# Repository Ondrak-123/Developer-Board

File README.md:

# RP2040 Developer Board
This project was great for learning something about the RP2040 ecosystem, great thing about this dev board is 16MB FLASH and 30 GPIOS.
You can use this developer board in breadboards, custom builds and any other way you can think of!

_**Featuring:**_
 
**MCU: Dual-core Arm Cortex-M0+ @ 133MHz.**

**Storage: 16MB (128Mbit) SPI Flash**

**Power: 3.3V LDO (MCP1700), up to 250mA.**

**Interface: USB-C 2.0 for programming and power.**

**Button for easy flashing.**

**This build features 0402 and QFLN parts so you will need some experience, steady hands, stencil and a solder paste/flux.**

**HOW TO FLASH:**
- This board supports the standard RP2040 bootloader
- Connect the board to your PC via USB-C
- Hold down the BOOTSEL button.
- The board will appear as a mass storage device
- Drag and drop your .uf2 file

**BOM:**

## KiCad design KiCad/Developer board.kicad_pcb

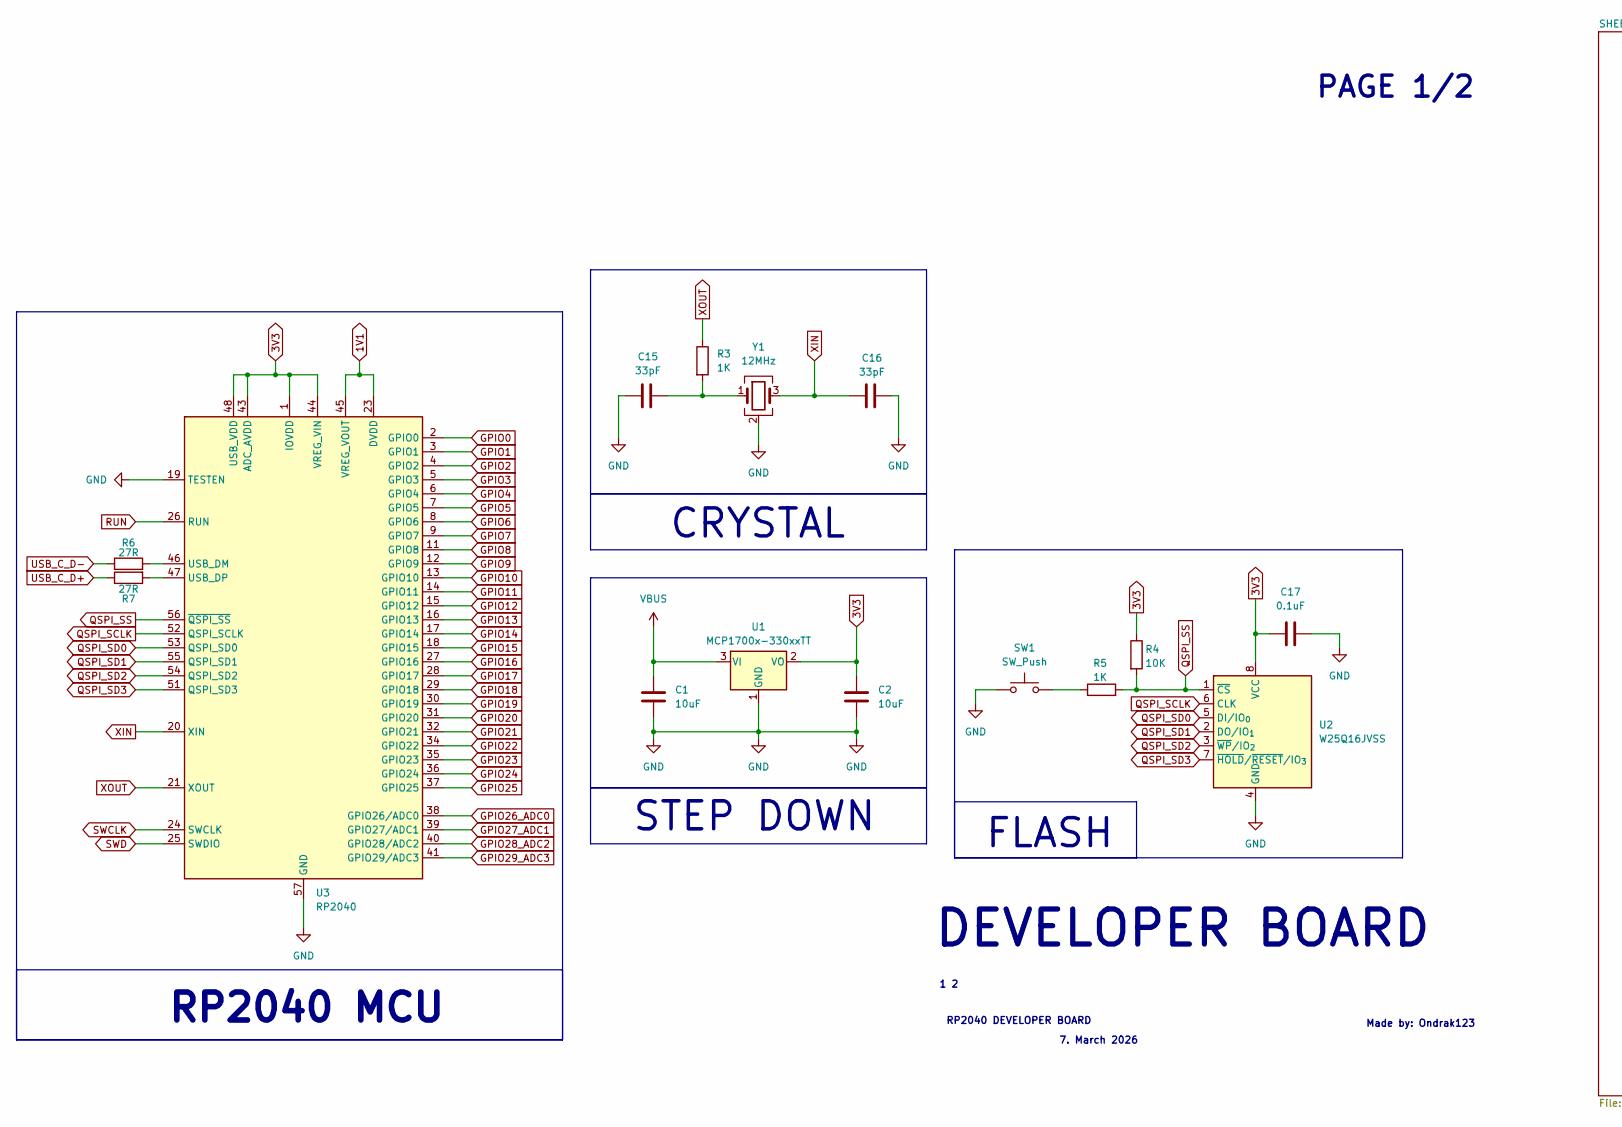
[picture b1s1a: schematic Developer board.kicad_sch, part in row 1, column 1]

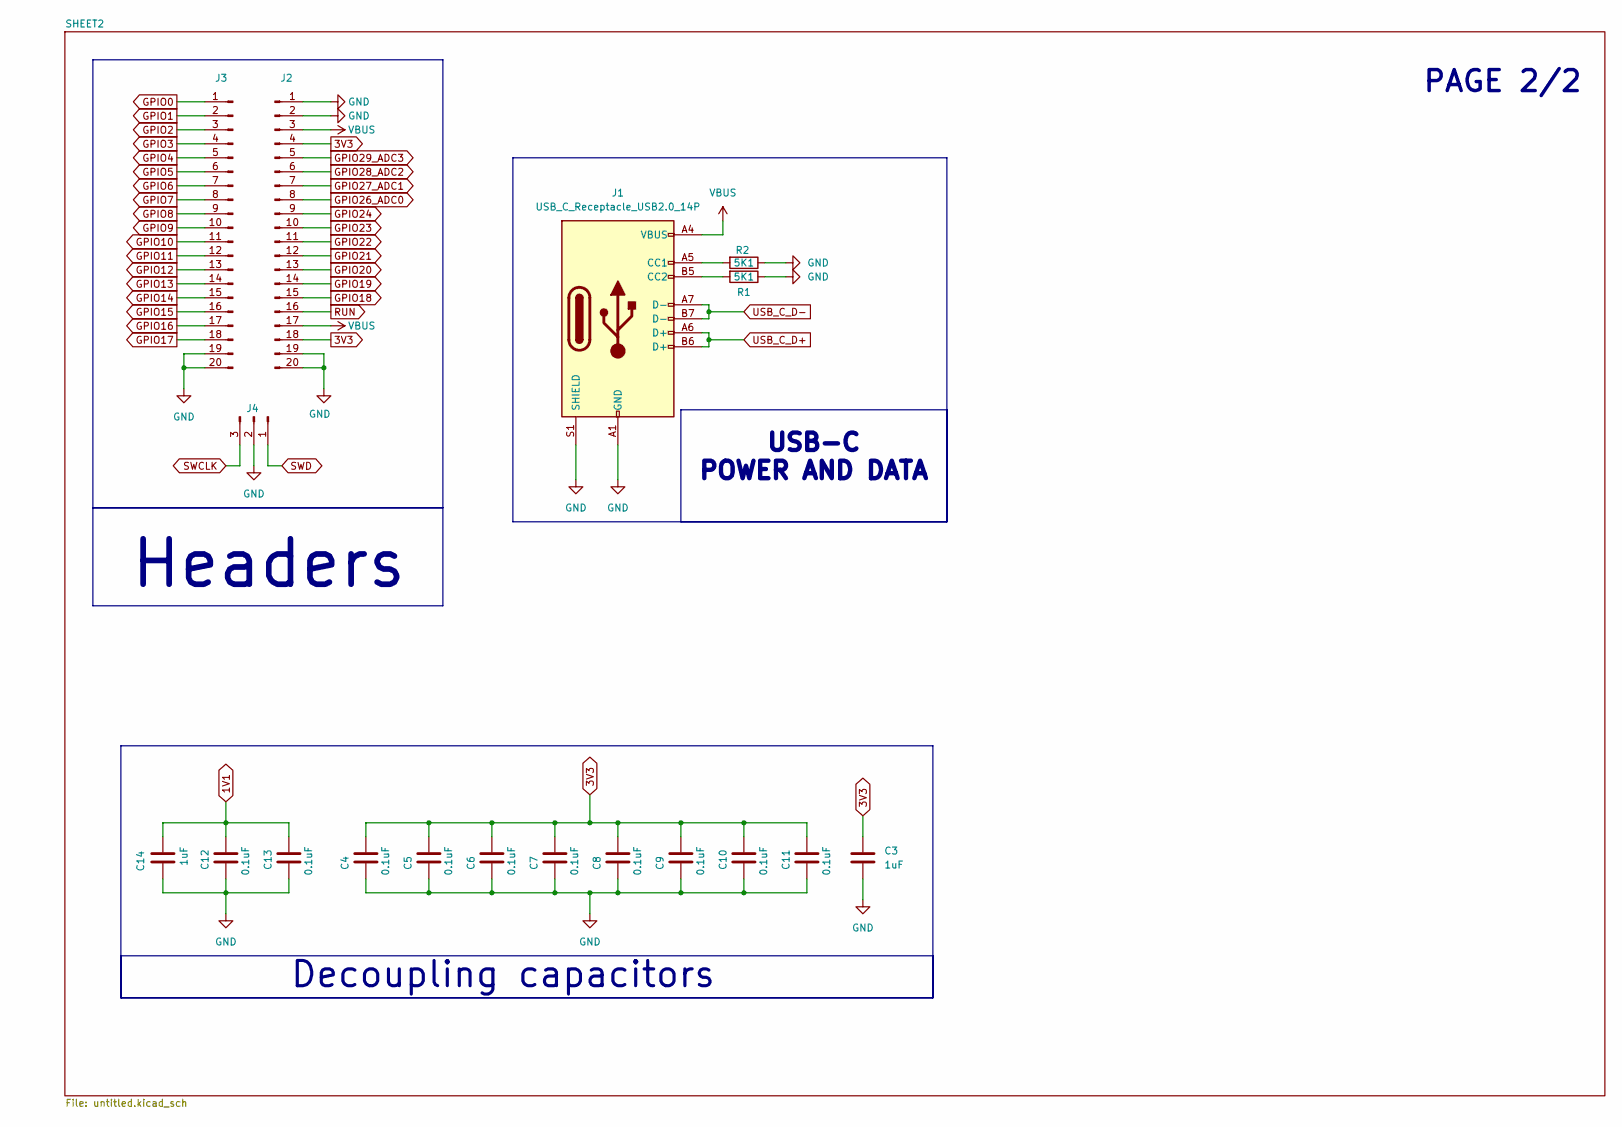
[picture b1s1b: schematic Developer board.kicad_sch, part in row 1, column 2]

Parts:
C1, C2: 10uF; C_0603_1608Metric
C3, C14: 1uF; C_0603_1608Metric
C4, C5, C6, C7, C8, C9, C10, C11, C12, C13, C17: 0.1uF; C_0402_1005Metric_Pad0.74x0.62mm_HandSolder
C15, C16: 33pF; C_0402_1005Metric_Pad0.74x0.62mm_HandSolder
J1: USB_C_Receptacle_USB2.0_14P; USB_C_Receptacle_GCT_USB4105-xx-A_16P_TopMnt_Horizontal
J2, J3: Conn_01x20_Pin; PinHeader_1x20_P2.54mm_Vertical
J4: Conn_01x03_Pin; PinHeader_1x03_P2.54mm_Vertical
R1, R2: 5K1; R_0402_1005Metric_Pad0.72x0.64mm_HandSolder
R3, R5: 1K; R_0402_1005Metric_Pad0.72x0.64mm_HandSolder
R4: 10K; R_0402_1005Metric_Pad0.72x0.64mm_HandSolder
R6, R7: 27R; R_0402_1005Metric_Pad0.72x0.64mm_HandSolder
SW1: SW_Push; SW_Push_SPST_NO_Alps_SKRK
U1: MCP1700x-330xxTT; SOT-23
U2: W25Q16JVSS; SOIC-8_5.3x5.3mm_P1.27mm
U3: RP2040; QFN-56-1EP_7x7mm_P0.4mm_EP3.2x3.2mm
Y1: 12MHz; Crystal_SMD_3225-4Pin_3.2x2.5mm_HandSoldering

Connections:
1V1: C12.1, C13.1, C14.1, U3.23 (DVDD), U3.45 (VREG_VOUT), U3.50 (DVDD)
3V3: C2.1, C3.1, C4.1, C5.1, C6.1, C7.1, C8.1, C9.1, C10.1, C11.1, C17.1, J2.4, J2.18, R4.1, U1.2 (VO), U2.8 (VCC), U3.1 (IOVDD), U3.10 (IOVDD), U3.22 (IOVDD), U3.33 (IOVDD), U3.42 (IOVDD), U3.43 (ADC_AVDD), U3.44 (VREG_VIN), U3.48 (USB_VDD), U3.49 (IOVDD)
GND: C1.2, C2.2, C3.2, C4.2, C5.2, C6.2, C7.2, C8.2, C9.2, C10.2, C11.2, C12.2, C13.2, C14.2, C15.1, C16.1, C17.2, J1.A1 (GND), J1.A12 (GND), J1.B1 (GND), J1.B12 (GND), J1.S1 (SHIELD), J2.1, J2.2, J2.19, J2.20, J3.19, J3.20, J4.2, R1.1, R2.1, SW1.1, U1.1 (GND), U2.4 (GND), U3.19 (TESTEN), U3.57 (GND), Y1.2 (G), Y1.4 (G)
GPIO0: J3.1, U3.2 (GPIO0)
GPIO1: J3.2, U3.3 (GPIO1)
GPIO2: J3.3, U3.4 (GPIO2)
GPIO3: J3.4, U3.5 (GPIO3)
GPIO4: J3.5, U3.6 (GPIO4)
GPIO5: J3.6, U3.7 (GPIO5)
GPIO6: J3.7, U3.8 (GPIO6)
GPIO7: J3.8, U3.9 (GPIO7)
GPIO8: J3.9, U3.11 (GPIO8)
GPIO9: J3.10, U3.12 (GPIO9)
GPIO10: J3.11, U3.13 (GPIO10)
GPIO11: J3.12, U3.14 (GPIO11)
GPIO12: J3.13, U3.15 (GPIO12)
GPIO13: J3.14, U3.16 (GPIO13)
GPIO14: J3.15, U3.17 (GPIO14)
GPIO15: J3.16, U3.18 (GPIO15)
GPIO16: J3.17, U3.27 (GPIO16)
GPIO17: J3.18, U3.28 (GPIO17)
GPIO18: J2.15, U3.29 (GPIO18)
GPIO19: J2.14, U3.30 (GPIO19)
GPIO20: J2.13, U3.31 (GPIO20)
GPIO21: J2.12, U3.32 (GPIO21)
GPIO22: J2.11, U3.34 (GPIO22)
GPIO23: J2.10, U3.35 (GPIO23)
GPIO24: J2.9, U3.36 (GPIO24)
GPIO25: U3.37 (GPIO25)
GPIO26_ADC0: J2.8, U3.38 (GPIO26/ADC0)
GPIO27_ADC1: J2.7, U3.39 (GPIO27/ADC1)
GPIO28_ADC2: J2.6, U3.40 (GPIO28/ADC2)
GPIO29_ADC3: J2.5, U3.41 (GPIO29/ADC3)
unnamed: C15.2, R3.2, Y1.1
unnamed: J1.A5 (CC1), R2.2
unnamed: J1.B5 (CC2), R1.2
unnamed: R5.1, SW1.2
unnamed: R6.2, U3.46 (USB_DM)
unnamed: R7.2, U3.47 (USB_DP)
QSPI_SCLK: U2.6 (CLK), U3.52 (QSPI_SCLK)
QSPI_SD0: U2.5 (DI/IO_{0}), U3.53 (QSPI_SD0)
QSPI_SD1: U2.2 (DO/IO_{1}), U3.55 (QSPI_SD1)
QSPI_SD2: U2.3 (~WP/IO_{2}), U3.54 (QSPI_SD2)
QSPI_SD3: U2.7 (~HOLD/~RESET/IO_{3}), U3.51 (QSPI_SD3)
QSPI_SS: R4.2, R5.2, U2.1 (~CS), U3.56 (~QSPI_SS)
RUN: J2.16, U3.26 (RUN)
SWCLK: J4.3, U3.24 (SWCLK)
SWD: J4.1, U3.25 (SWDIO)
USB_C_D+: J1.A6 (D+), J1.B6 (D+), R7.1
USB_C_D-: J1.A7 (D-), J1.B7 (D-), R6.1
VBUS: C1.1, J1.A4 (VBUS), J1.A9 (VBUS), J1.B4 (VBUS), J1.B9 (VBUS), J2.3, J2.17, U1.3 (VI)
XIN: C16.2, U3.20 (XIN), Y1.3
XOUT: R3.1, U3.21 (XOUT)

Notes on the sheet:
STEP DOWN
Made by: Ondrak123
PAGE 2/2
1 2
RP2040 MCU
PAGE 1/2
CRYSTAL
DEVELOPER BOARD
FLASH
Headers
7. March 2026
Decoupling capacitors
USB-C POWER AND DATA
RP2040 DEVELOPER BOARD

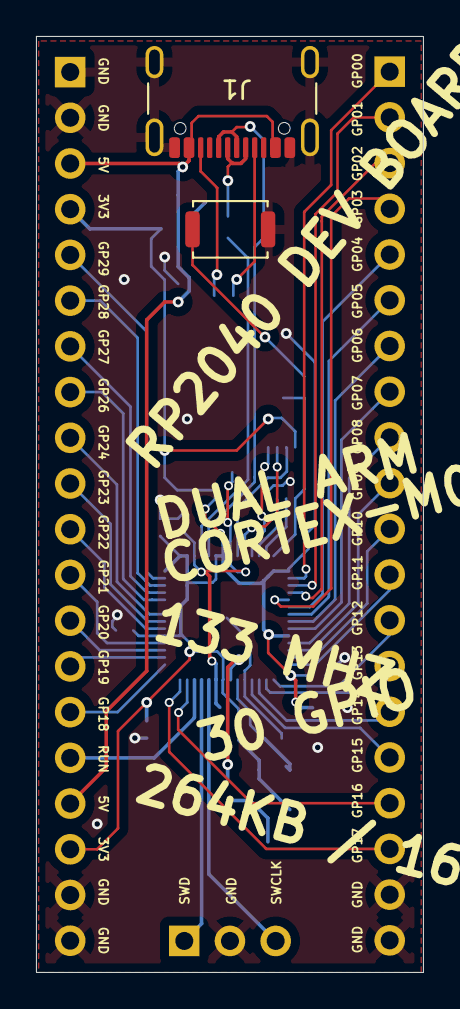
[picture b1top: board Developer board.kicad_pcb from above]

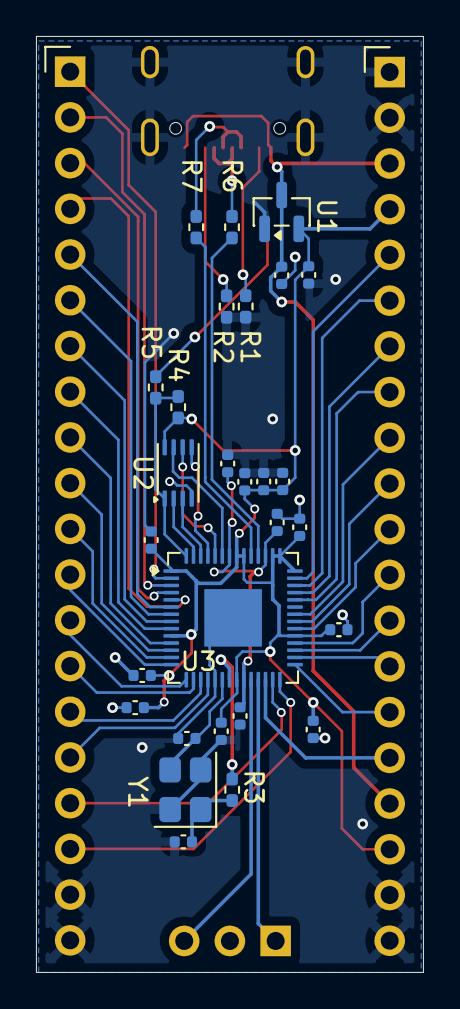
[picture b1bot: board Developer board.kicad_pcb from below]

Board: 2 copper layers, 21.5 x 52.0 mm, 33 parts (30 on the bottom side), 52 nets.

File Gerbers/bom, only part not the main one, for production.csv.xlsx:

Designator,LCSC Part,Quantity,Value,Footprint
C1, C2,C15525,2,10uF,0402
C10, C11, C12, C13, C17, C4, C5, C6, C7, C8, C9,C1525,11,0.1uF,0402
C14, C3,C52923,2,1uF,0402
C15, C16,C32162,2,33pF,0402
J1,C719112,1,USB-C 2.0 (16P),USB-C-16P
J2, J3,C124356,2,Conn_01x20,2.54mm-1x20
J4,C2818960,1,Conn_01x03,2.54mm-1x03
R1, R2,C25905,2,5.1k,0402
R3, R5,C25076,2,1k,0402
R4,C25744,1,10k,0402
R6, R7,C25102,2,27R,0402
SW1,C6230,1,Tactile Switch,3x6mm SMD
U1,C517721,1,MCP1700T-3302E/TT,SOT-23
U2,C2040,1,RP2040,QFN-56
U3,C82490,1,W25Q128JVSIQ,SOIC-8
Y1,C90039,1,12MHz Crystal,3225-4P

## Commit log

2026-03-11 Upload
2026-03-11 Update assembly service instructions in readme
2026-03-11 Update README with RP2040 board details
    Added detailed specifications and flashing instructions for the RP2040 Developer Board.
2026-03-11 gerbers update
2026-03-11 slight text update
2026-03-11 graphics update
